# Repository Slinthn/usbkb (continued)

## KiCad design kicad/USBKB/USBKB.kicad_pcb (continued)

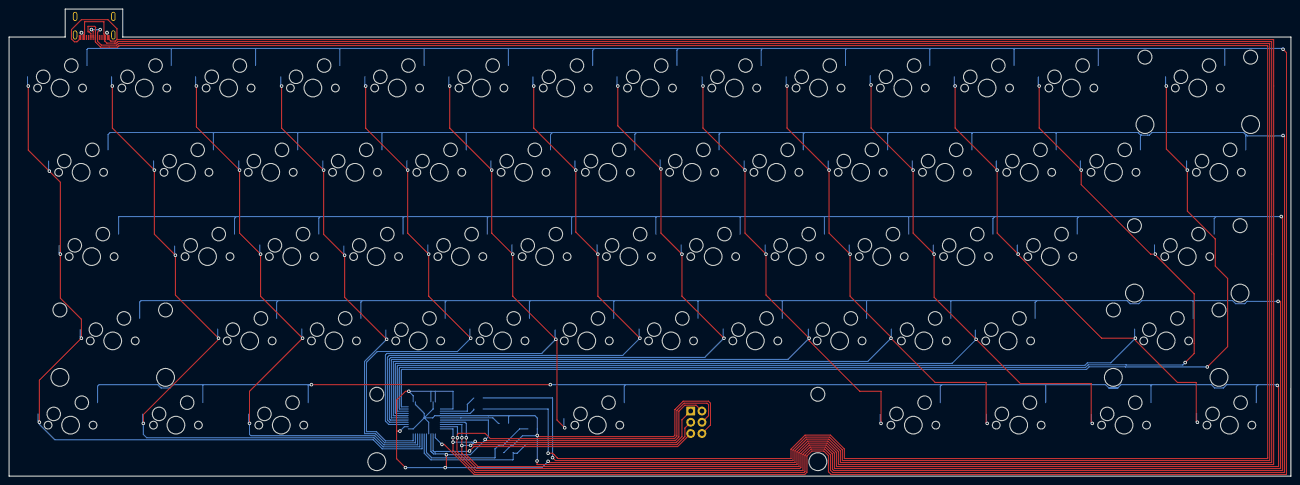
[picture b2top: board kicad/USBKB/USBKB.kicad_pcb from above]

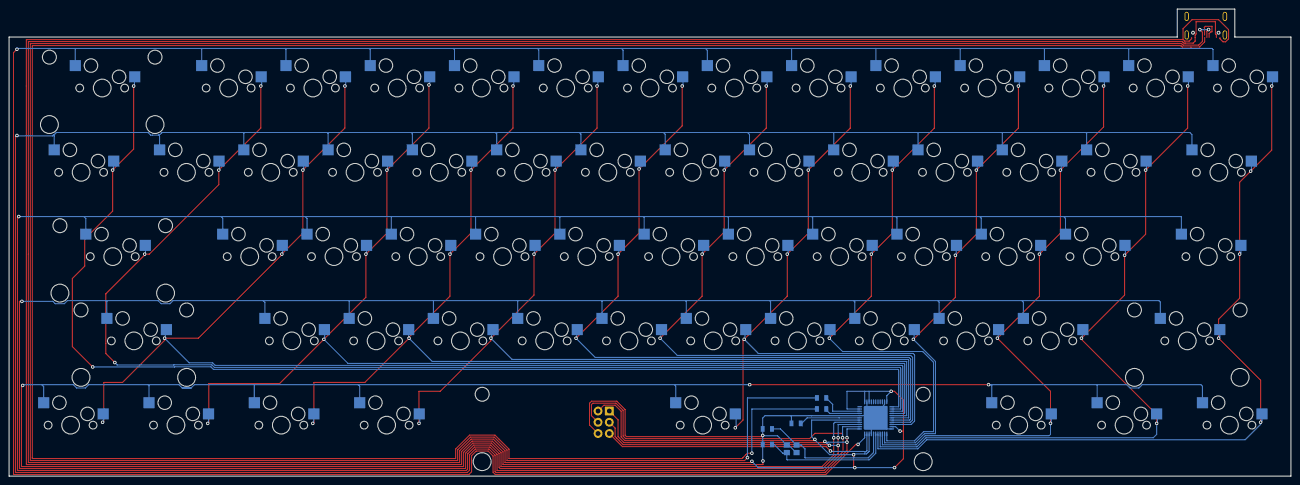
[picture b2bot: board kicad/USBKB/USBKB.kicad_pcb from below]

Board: 2 copper layers, 289.8 x 105.6 mm, 70 parts (7 on the bottom side), 29 nets.

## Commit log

2022-11-12 Initial commit - certain source code, KiCAD files, documentation
2022-12-01 Started USB code and changed to C
2022-12-01 Began USB endpoint 0 configuration
2022-12-09 USB setup packet implementation progress
2022-12-09 assemble.bat folder hotfix
2022-12-09 More USB descriptors and ipecmd debugging
2022-12-10 Fixed USB descriptors and shows up as HID now
2022-12-10 Device sends f keypress on connection
2022-12-11 USB keysend works and cleaner code
2022-12-11 Cleaned code and TODO, and tried keypress using interrupt
2022-12-11 WASD keys
2022-12-12 Began keyboard matrix implementation & neater code
2022-12-14 Began work on ATMEGA32U4-MU footprint
2022-12-22 Work on PCB footprints
2022-12-22 Work on pricing begun
2022-12-23 Fixed keyboard code and added all keys
2022-12-29 Schematic and footprint complete
2022-12-29 Fixed USB-C connector in schematic
2022-12-29 Began PCB alignment
2023-01-01 Plate and PCB completed, pricing list updated with shipping fees
2023-01-02 Renamed folders and updated pricing excel
2023-01-02 Renamed code folder and fixed kicad .gitignore
2023-01-02 Removed backup file for kicad
2023-01-08 Home page, login & signup page, backend almost complete
2023-01-08 Work on case and PCB (now completely rectangular)
2023-01-08 Homepage design
2023-01-17 Website design
2023-01-22 Attempt at WS2812B lighting
2023-01-23 Programmer code setup
2023-01-26 Finally LED works
2023-01-28 Code beauty and led strip takes up small current. RGB wave
2023-02-05 Changes to PCB layout, design, diodes, leds, code, everything
2023-02-09 PCB design and schematic
2023-02-26 PCB done
2023-03-19 Case design complete
